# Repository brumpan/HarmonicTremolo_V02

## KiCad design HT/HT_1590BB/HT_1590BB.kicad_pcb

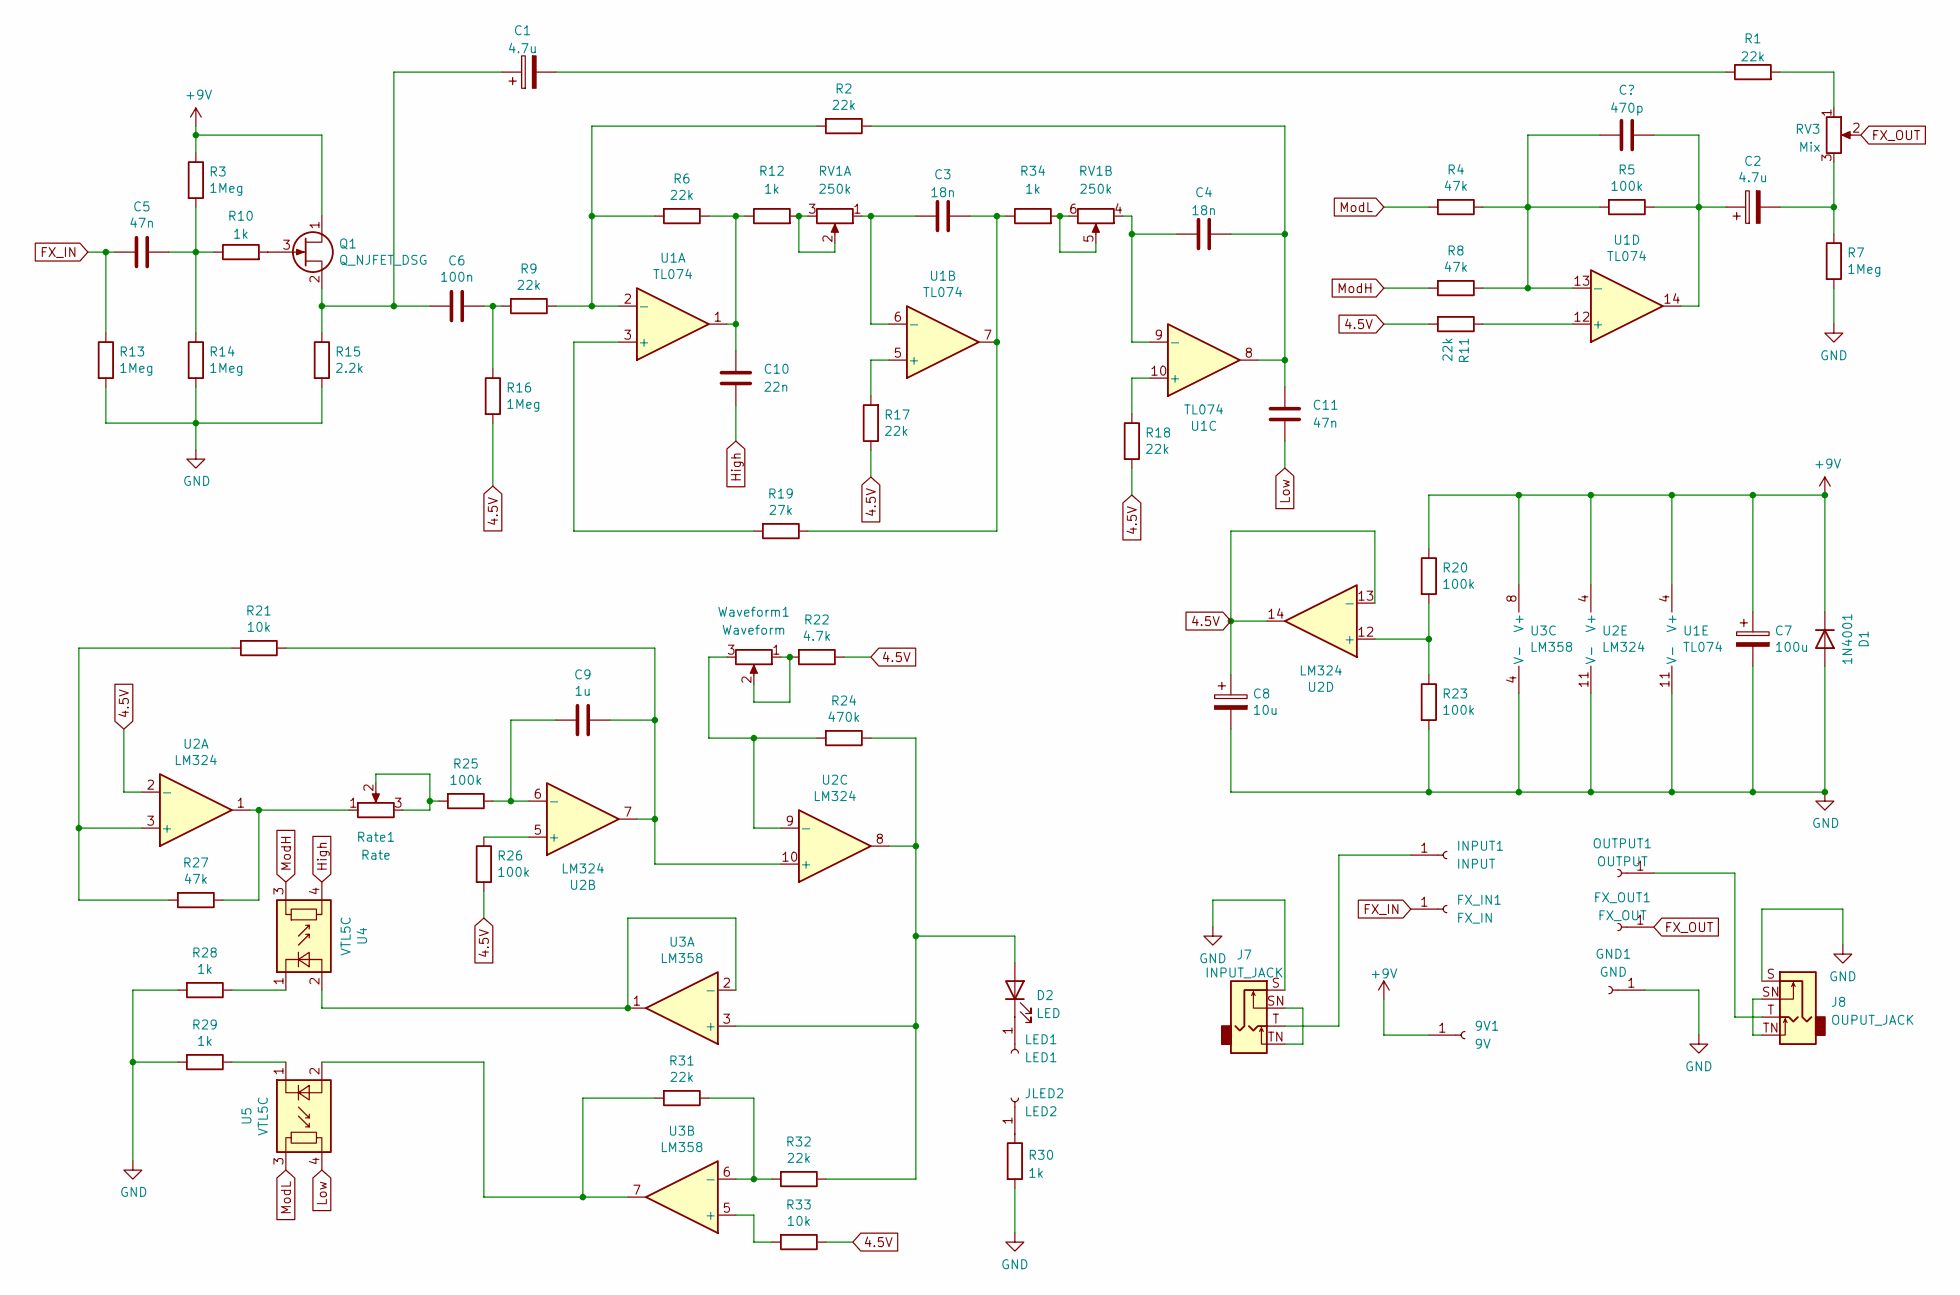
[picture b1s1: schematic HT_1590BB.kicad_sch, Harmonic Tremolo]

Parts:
9V1: 9V; SolderWire-1sqmm_1x01_D1.4mm_OD2.7mm
C1, C2: 4.7u; CP_Radial_D5.0mm_P2.00mm
C3, C4: 18n; C_Rect_L7.0mm_W2.5mm_P5.00mm
C5, C11: 47n; C_Rect_L7.0mm_W2.5mm_P5.00mm
C6: 100n; C_Rect_L7.0mm_W2.5mm_P5.00mm
C7: 100u; CP_Radial_D6.3mm_P2.50mm
C8: 10u; CP_Radial_D5.0mm_P2.00mm
C9: 1u; C_Rect_L7.0mm_W2.5mm_P5.00mm
C10: 22n; C_Rect_L7.0mm_W2.5mm_P5.00mm
D1: 1N4001; D_DO-41_SOD81_P10.16mm_Horizontal
D2: LED; LED_D5.0mm
FX_IN1: FX_IN; SolderWire-1sqmm_1x01_D1.4mm_OD2.7mm
FX_OUT1: FX_OUT; SolderWire-1sqmm_1x01_D1.4mm_OD2.7mm
GND1: GND; SolderWire-1sqmm_1x01_D1.4mm_OD2.7mm
INPUT1: INPUT; SolderWire-1sqmm_1x01_D1.4mm_OD2.7mm
J7: INPUT_JACK; Jack_6.35mm_Neutrik_NMJ4HCD2_Horizontal
J8: OUPUT_JACK; Jack_6.35mm_Neutrik_NMJ4HCD2_Horizontal
JLED2: LED2; SolderWire-1sqmm_1x01_D1.4mm_OD2.7mm
LED1: LED1; SolderWire-1sqmm_1x01_D1.4mm_OD2.7mm
OUTPUT1: OUTPUT; SolderWire-1sqmm_1x01_D1.4mm_OD2.7mm
Q1: Q_NJFET_DSG; TO-92_Inline_Wide
R1, R2, R6, R9, R11, R17, R18, R31, R32: 22k; R_Axial_DIN0207_L6.3mm_D2.5mm_P10.16mm_Horizontal
R3, R7, R13, R14, R16: 1Meg; R_Axial_DIN0207_L6.3mm_D2.5mm_P10.16mm_Horizontal
R4, R8, R27: 47k; R_Axial_DIN0207_L6.3mm_D2.5mm_P10.16mm_Horizontal
R5, R20, R23, R25, R26: 100k; R_Axial_DIN0207_L6.3mm_D2.5mm_P10.16mm_Horizontal
R10, R12, R28, R29, R30, R34: 1k; R_Axial_DIN0207_L6.3mm_D2.5mm_P10.16mm_Horizontal
R15: 2.2k; R_Axial_DIN0207_L6.3mm_D2.5mm_P10.16mm_Horizontal
R19: 27k; R_Axial_DIN0207_L6.3mm_D2.5mm_P10.16mm_Horizontal
R21, R33: 10k; R_Axial_DIN0207_L6.3mm_D2.5mm_P10.16mm_Horizontal
R22: 4.7k; R_Axial_DIN0207_L6.3mm_D2.5mm_P10.16mm_Horizontal
R24: 470k; R_Axial_DIN0207_L6.3mm_D2.5mm_P10.16mm_Horizontal
RV1: 250k; Alpha_16mm_PCB_RA_Dual
RV3: Mix; Alpha_16mm_PCB_RA
Rate1: Rate; Alpha_16mm_PCB_RA
U1: TL074; DIP-14_W7.62mm_Socket
U2: LM324; DIP-14_W7.62mm_Socket
U3: LM358; DIP-8_W7.62mm_Socket
U4, U5: VTL5C; Vactrol
Waveform1: Waveform; Alpha_16mm_PCB_RA

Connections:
4.5V: C8.1, R11.2, R16.2, R17.1, R18.2, R22.1, R26.2, R33.1, U2.2 (-), U2.13 (-), U2.14
+9V: 9V1.1, C7.1, D1.1 (K), Q1.1 (D), R3.1, R20.1, U1.4 (V+), U2.4 (V+), U3.8 (V+)
FX_IN: C5.2, FX_IN1.1, R13.1; also elsewhere on the board
FX_OUT: FX_OUT1.1, RV3.2; also elsewhere on the board
GND: C7.2, C8.2, D1.2 (A), GND1.1, J7.S, J8.S, R7.2, R13.2, R14.2, R15.2, R23.2, R28.2, R29.2, R30.2, U1.11 (V-), U2.11 (V-), U3.4 (V-); also elsewhere on the board
High: C10.2, U4.4
Low: C11.2, U5.4
ModH: R8.2, U4.3
ModL: R4.2, U5.3
unnamed: C1.1, C6.2, Q1.2 (S), R15.1
unnamed: C1.2, R1.1
unnamed: C2.1, R5.1, U1.14
unnamed: C2.2, R7.1, RV3.3
unnamed: C3.1, RV1.1, U1.6 (-)
unnamed: C3.2, R19.1, R34.1, U1.7
unnamed: C4.1, RV1.4, U1.9 (-)
unnamed: C4.2, C11.1, R2.1, U1.8
unnamed: C5.1, R3.2, R10.1, R14.1
unnamed: C6.1, R9.2, R16.1
unnamed: C9.1, R21.1, U2.7, U2.10 (+)
unnamed: C9.2, R25.1, U2.6 (-)
unnamed: D2.1 (K), LED1.1
unnamed: D2.2 (A), R24.1, R32.1, U2.8, U3.3 (+)
unnamed 23: INPUT1.1, J7.T; also elsewhere on the board
unnamed: J7.SN, J7.TN
unnamed: J8.SN, J8.TN
unnamed 26: J8.T, OUTPUT1.1; also elsewhere on the board
unnamed: Q1.3 (G), R10.2
unnamed: R1.2, RV3.1
unnamed: R2.2, R6.2, R9.1, U1.2 (-)
unnamed: R4.1, R5.2, R8.1, U1.13 (-)
unnamed: R11.1, U1.12 (+)
unnamed: C10.1, R6.1, R12.1, U1.1
unnamed: R12.2, RV1.2, RV1.3
unnamed: R17.2, U1.5 (+)
unnamed: R18.1, U1.10 (+)
unnamed: R19.2, U1.3 (+)
unnamed: R20.2, R23.1, U2.12 (+)
unnamed: R21.2, R27.2, U2.3 (+)
unnamed: R22.2, Waveform1.1, Waveform1.2
unnamed: R24.2, U2.9 (-), Waveform1.3
unnamed: R25.2, Rate1.2, Rate1.3
unnamed: R26.1, U2.5 (+)
unnamed: R27.1, Rate1.1, U2.1
unnamed: R28.1, U4.1 (-)
unnamed: R29.1, U5.1 (-)
unnamed 46: JLED2.1, R30.1; also elsewhere on the board
unnamed: R31.1, R32.2, U3.6 (-)
unnamed: R31.2, U3.7, U5.2 (+)
unnamed: R33.2, U3.5 (+)
unnamed: R34.2, RV1.5, RV1.6
unnamed: U3.1, U3.2 (-), U4.2 (+)

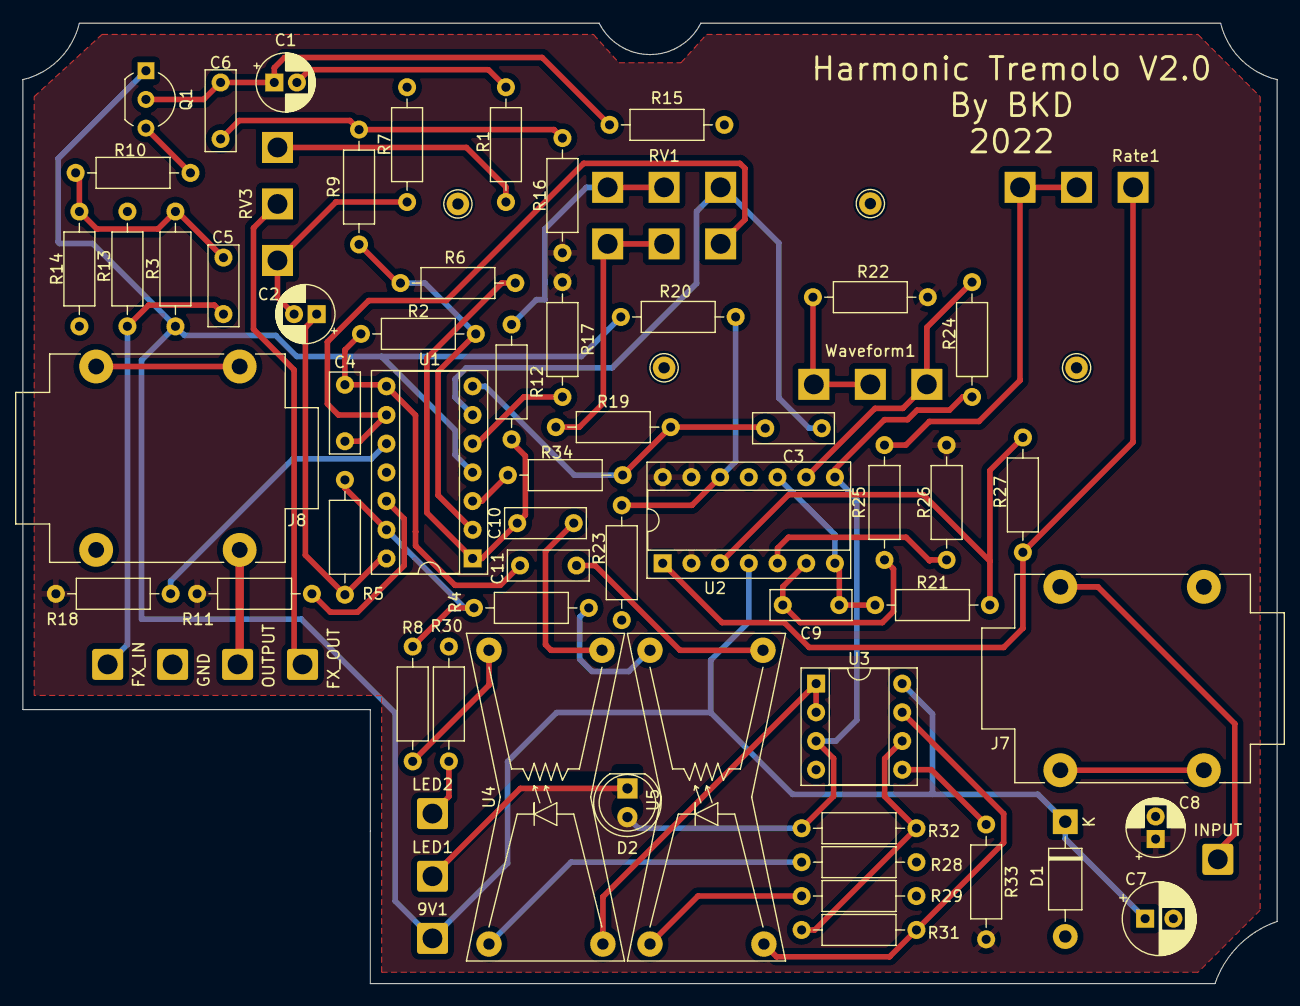
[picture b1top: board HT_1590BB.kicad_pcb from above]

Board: 2 copper layers, 111.0 x 85.0 mm, 71 parts (0 on the bottom side), 52 nets.

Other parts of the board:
DRL1, DRL1#2, DRL2, DRL3: Pin_D1.0mm_L10.0mm
FX_IN: FX_IN; SolderWire-1sqmm_1x01_D1.4mm_OD2.7mm
FX_OUT: FX_OUT; SolderWire-1sqmm_1x01_D1.4mm_OD2.7mm
GND: GND; SolderWire-1sqmm_1x01_D1.4mm_OD2.7mm
INPUT: INPUT; SolderWire-1sqmm_1x01_D1.4mm_OD2.7mm
LED2: LED2; SolderWire-1sqmm_1x01_D1.4mm_OD2.7mm
OUTPUT: OUTPUT; SolderWire-1sqmm_1x01_D1.4mm_OD2.7mm

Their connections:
FX_IN: FX_IN.1; also elsewhere on the board
FX_OUT: FX_OUT.1; also elsewhere on the board
GND: GND.1; also elsewhere on the board
unnamed 23: INPUT.1; also elsewhere on the board
unnamed 26: OUTPUT.1; also elsewhere on the board
unnamed 46: LED2.1; also elsewhere on the board
